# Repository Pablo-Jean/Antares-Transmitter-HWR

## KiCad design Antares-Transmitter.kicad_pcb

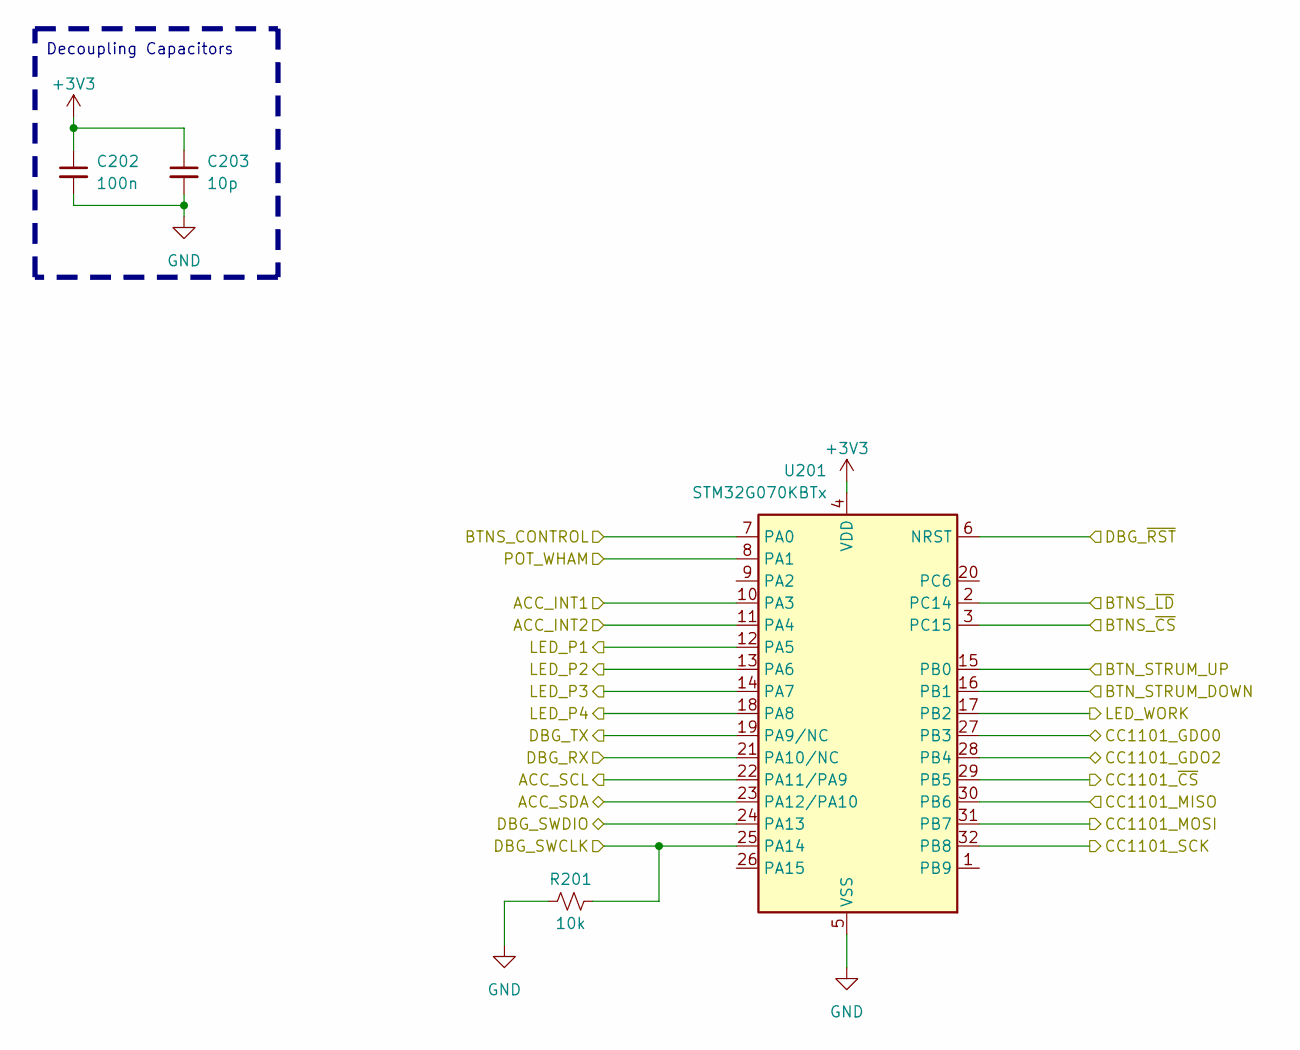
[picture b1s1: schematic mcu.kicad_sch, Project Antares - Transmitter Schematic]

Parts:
C202: 100n; C_0603_1608Metric; LCSC C14663
C203: 10p; C_0603_1608Metric; LCSC C1634
R201: 10k; R_0603_1608Metric; LCSC C25804
U201: STM32G070KBTx; LQFP-32_7x7mm_P0.8mm; LCSC C529339

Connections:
+3V3: C202.1, C203.1, U201.4 (VDD); also elsewhere on the board
/Accelerometer/ACC_INT1: U201.10 (PA3); also elsewhere on the board
/Accelerometer/ACC_INT2: U201.11 (PA4); also elsewhere on the board
/Accelerometer/ACC_SCL: U201.22 (PA11/PA9); also elsewhere on the board
/Accelerometer/ACC_SDA: U201.23 (PA12/PA10); also elsewhere on the board
/Control Buttons/BTNS_CONTROL: U201.7 (PA0); also elsewhere on the board
/Control Buttons/LED_WORK: U201.17 (PB2); also elsewhere on the board
/Debugging/DBG_RX: U201.21 (PA10/NC); also elsewhere on the board
/Debugging/DBG_SWCLK: R201.2, U201.25 (PA14); also elsewhere on the board
/Debugging/DBG_SWDIO: U201.24 (PA13); also elsewhere on the board
/Debugging/DBG_TX: U201.19 (PA9/NC); also elsewhere on the board
/Debugging/DBG_~RST: U201.6 (NRST); also elsewhere on the board
/LEDs/LED_P1: U201.12 (PA5); also elsewhere on the board
/LEDs/LED_P2: U201.13 (PA6); also elsewhere on the board
/LEDs/LED_P3: U201.14 (PA7); also elsewhere on the board
/LEDs/LED_P4: U201.18 (PA8); also elsewhere on the board
/MCU/BTN_STRUM_DOWN: U201.16 (PB1); also elsewhere on the board
/MCU/BTN_STRUM_UP: U201.15 (PB0); also elsewhere on the board
/MCU/CC1101_GDO0: U201.27 (PB3); also elsewhere on the board
/MCU/CC1101_GDO2: U201.28 (PB4); also elsewhere on the board
/MCU/CC1101_MOSI: U201.31 (PB7); also elsewhere on the board
/MCU/CC1101_~CS: U201.29 (PB5); also elsewhere on the board
/MCU/POT_WHAM: U201.8 (PA1); also elsewhere on the board
/Notes/HC165_DO: U201.30 (PB6); also elsewhere on the board
/Notes/HC165_LOAD: U201.2 (PC14); also elsewhere on the board
/Notes/HC165_SCK: U201.32 (PB8); also elsewhere on the board
/Notes/HC165_~CS: U201.3 (PC15); also elsewhere on the board
GND: C202.2, C203.2, R201.1, U201.5 (VSS); also elsewhere on the board

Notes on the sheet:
Decoupling Capacitors

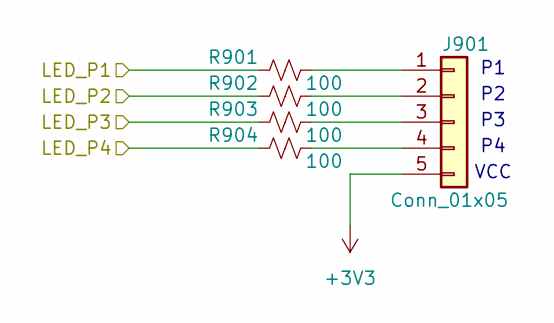
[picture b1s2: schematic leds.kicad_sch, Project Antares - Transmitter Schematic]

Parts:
J901: Conn_01x05; JST_XH_S5B-XH-A-1_1x05_P2.50mm_Horizontal; LCSC C2845508
R901, R902, R903, R904: 100; R_0603_1608Metric; LCSC C22775

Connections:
+3V3: J901.5; also elsewhere on the board
/LEDs/LED_P1: R901.1; also elsewhere on the board
/LEDs/LED_P2: R902.1; also elsewhere on the board
/LEDs/LED_P3: R903.1; also elsewhere on the board
/LEDs/LED_P4: R904.1; also elsewhere on the board
unnamed: J901.1, R901.2
unnamed: J901.2, R902.2
unnamed: J901.3, R903.2
unnamed: J901.4, R904.2

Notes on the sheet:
VCC

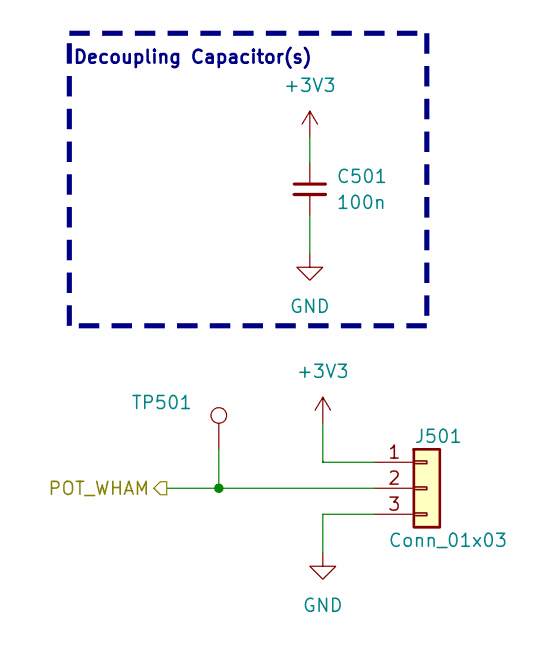
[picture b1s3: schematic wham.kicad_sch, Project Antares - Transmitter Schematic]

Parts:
C501: 100n; C_0603_1608Metric; LCSC C14663
J501: Conn_01x03; JST_XH_S3B-XH-A-1_1x03_P2.50mm_Horizontal; LCSC C2845506
TP501: TestPoint; TestPoint_Pad_D1.5mm

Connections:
+3V3: C501.1, J501.1; also elsewhere on the board
/MCU/POT_WHAM: J501.2, TP501.1; also elsewhere on the board
GND: C501.2, J501.3; also elsewhere on the board

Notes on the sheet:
Decoupling Capacitor(s)

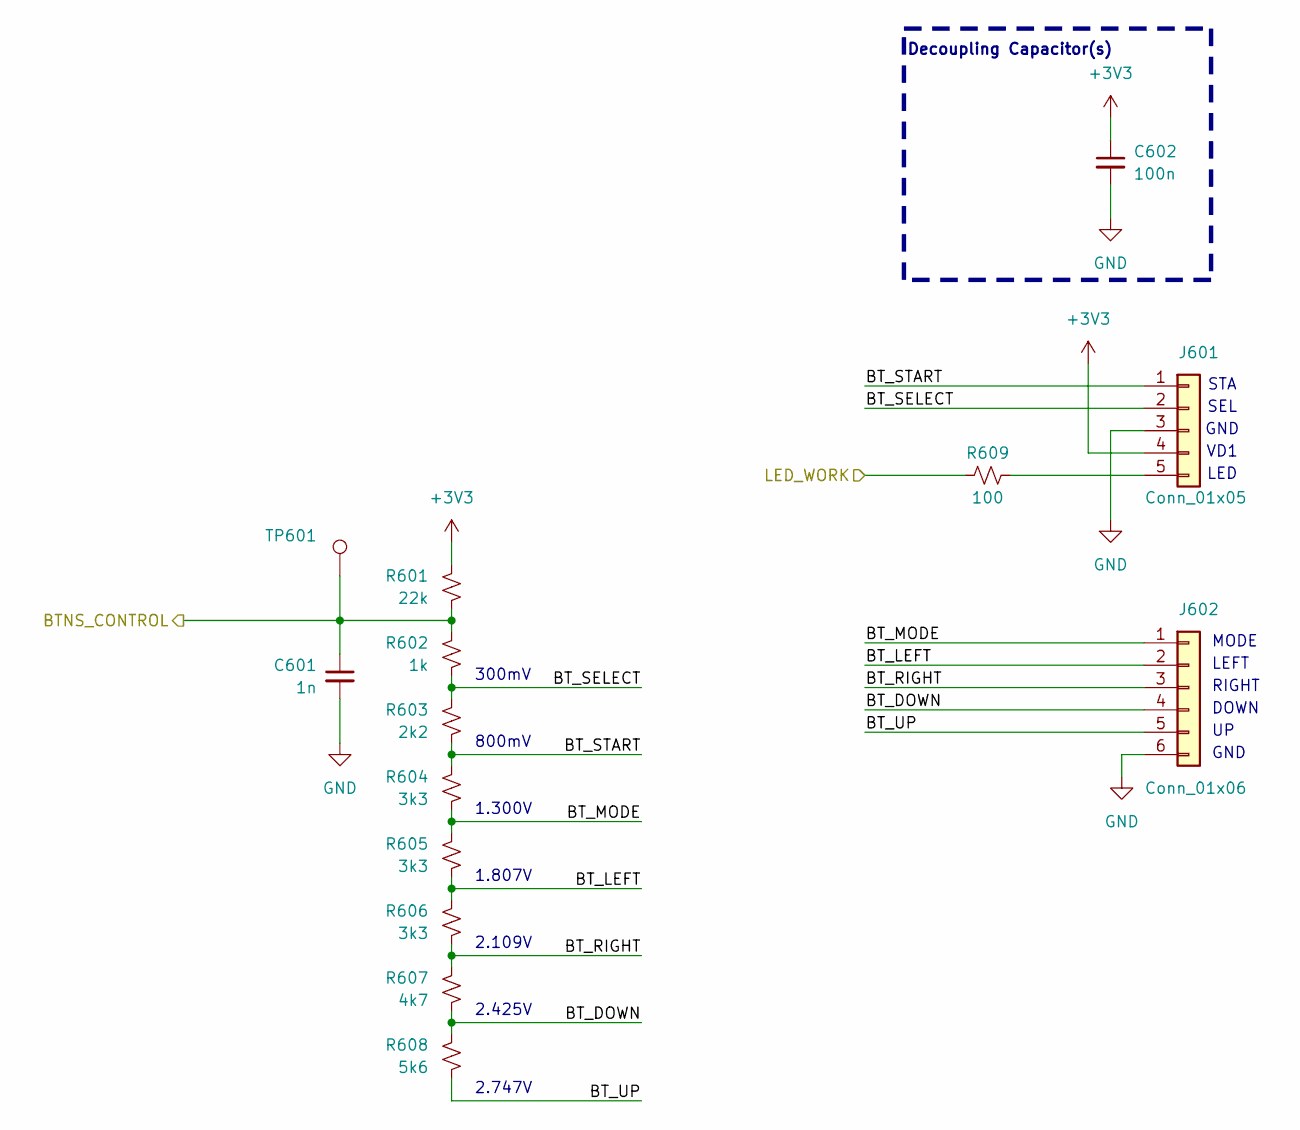
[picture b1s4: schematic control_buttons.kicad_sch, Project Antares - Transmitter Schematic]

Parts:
C601: 1n; C_0603_1608Metric; LCSC C1588
C602: 100n; C_0603_1608Metric; LCSC C14663
J601: Conn_01x05; JST_XH_S5B-XH-A-1_1x05_P2.50mm_Horizontal; LCSC C2845508
J602: Conn_01x06; JST_PH_S6B-PH-K_1x06_P2.00mm_Horizontal; LCSC C2908638
R601: 22k; R_0603_1608Metric; LCSC C31850
R602: 1k; R_0603_1608Metric; LCSC C21190
R603: 2k2; R_0603_1608Metric; LCSC C4190
R604, R605, R606: 3k3; R_0603_1608Metric; LCSC C22978
R607: 4k7; R_0603_1608Metric; LCSC C23162
R608: 5k6; R_0603_1608Metric; LCSC C23189
R609: 100; R_0603_1608Metric; LCSC C22775
TP601: TestPoint; TestPoint_Pad_D1.5mm

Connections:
+3V3: C602.1, J601.4, R601.1; also elsewhere on the board
/Control Buttons/BTNS_CONTROL: C601.1, R601.2, R602.1, TP601.1; also elsewhere on the board
/Control Buttons/BT_DOWN: J602.4, R607.2, R608.1
/Control Buttons/BT_LEFT: J602.2, R605.2, R606.1
/Control Buttons/BT_MODE: J602.1, R604.2, R605.1
/Control Buttons/BT_RIGHT: J602.3, R606.2, R607.1
/Control Buttons/BT_SELECT: J601.2, R602.2, R603.1
/Control Buttons/BT_START: J601.1, R603.2, R604.1
/Control Buttons/BT_UP: J602.5, R608.2
/Control Buttons/LED_WORK: R609.1; also elsewhere on the board
GND: C601.2, C602.2, J601.3, J602.6; also elsewhere on the board
unnamed: J601.5, R609.2

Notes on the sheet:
SEL
1.807V
VD1
RIGHT
MODE
800mV
Decoupling Capacitor(s)
1.300V
GND
LEFT
2.425V
STA
DOWN
300mV
LED
2.109V
2.747V

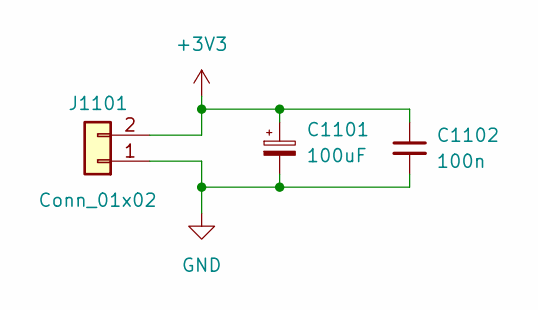
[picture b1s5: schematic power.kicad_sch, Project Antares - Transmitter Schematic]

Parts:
C1101: 100uF; CP_Elec_6.3x4.5; LCSC C5374787
C1102: 100n; C_0603_1608Metric; LCSC C14663
J1101: Conn_01x02; JST_XH_S2B-XH-A-1_1x02_P2.50mm_Horizontal; LCSC C33132

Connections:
+3V3: C1101.1, C1102.1, J1101.2; also elsewhere on the board
GND: C1101.2, C1102.2, J1101.1; also elsewhere on the board

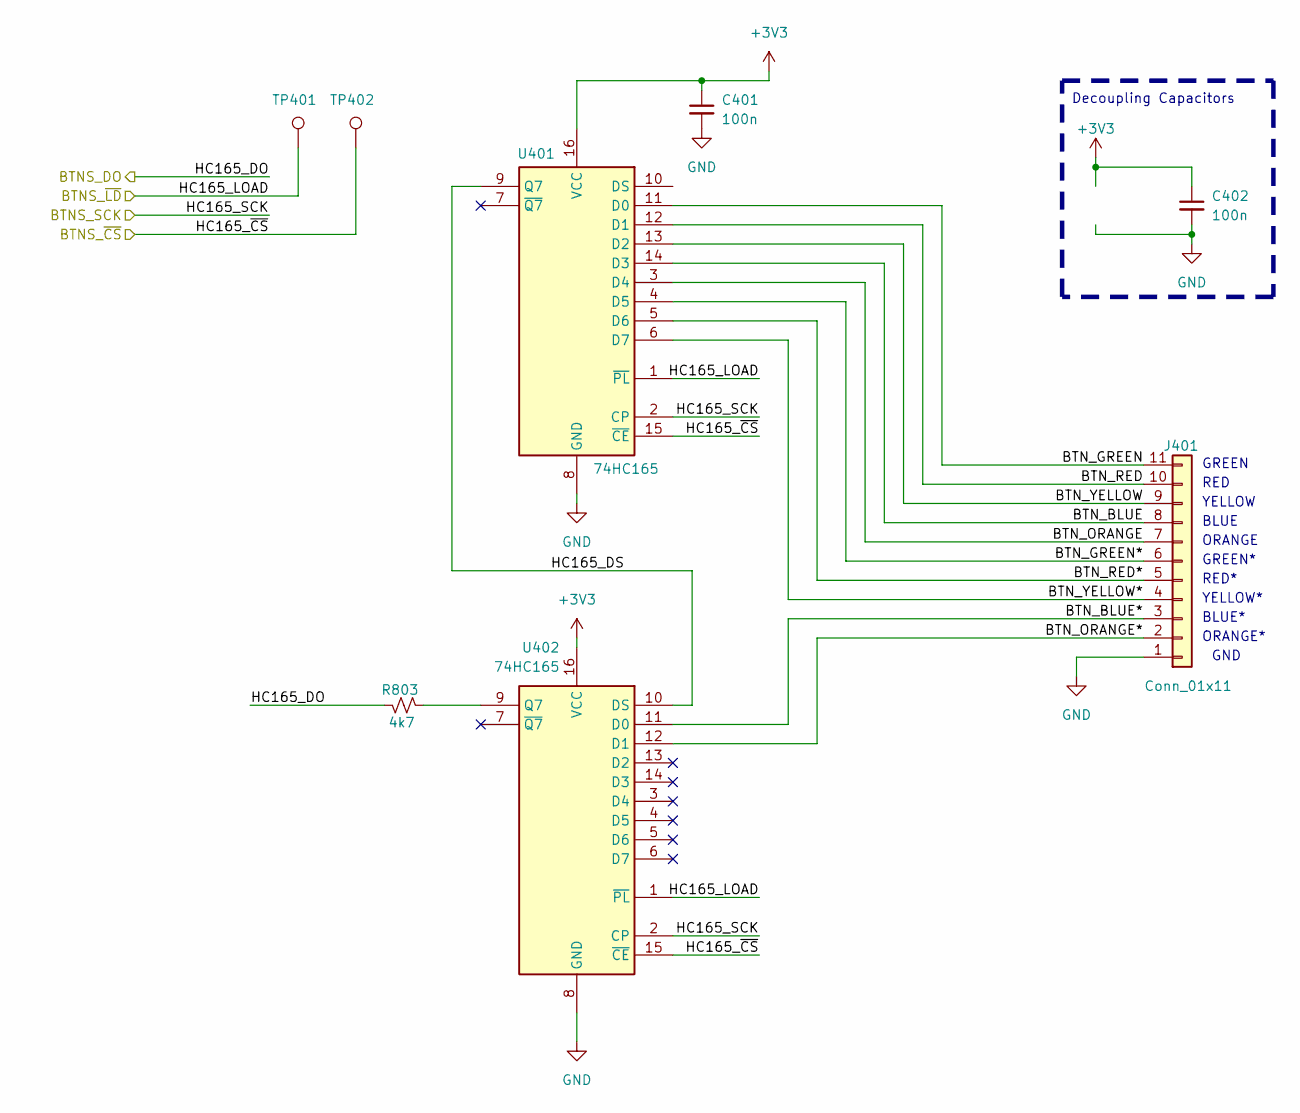
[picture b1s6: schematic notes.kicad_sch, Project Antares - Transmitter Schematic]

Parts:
C401, C402: 100n; C_0603_1608Metric; LCSC C14663
J401: Conn_01x11; JST_XH_S11B-XH-A-1_1x11_P2.50mm_Horizontal; LCSC C2845514
R803: 4k7; R_0603_1608Metric; LCSC C23162
TP401, TP402: TestPoint; TestPoint_Pad_D1.5mm
U401, U402: 74HC165; TSSOP-16_4.4x5mm_P0.65mm; LCSC C80696

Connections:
+3V3: C401.1, C402.1, U401.16 (VCC), U402.16 (VCC); also elsewhere on the board
/Notes/BTN_BLUE: J401.8, U401.14 (D3)
/Notes/BTN_BLUE*: J401.3, U402.11 (D0)
/Notes/BTN_GREEN: J401.11, U401.11 (D0)
/Notes/BTN_GREEN*: J401.6, U401.4 (D5)
/Notes/BTN_ORANGE: J401.7, U401.3 (D4)
/Notes/BTN_ORANGE*: J401.2, U402.12 (D1)
/Notes/BTN_RED: J401.10, U401.12 (D1)
/Notes/BTN_RED*: J401.5, U401.5 (D6)
/Notes/BTN_YELLOW: J401.9, U401.13 (D2)
/Notes/BTN_YELLOW*: J401.4, U401.6 (D7)
/Notes/HC165_DS: U401.9 (Q7), U402.10 (DS)
/Notes/HC165_LOAD: TP401.1, U401.1 (~PL), U402.1 (~PL); also elsewhere on the board
/Notes/HC165_SCK: U401.2 (CP), U402.2 (CP); also elsewhere on the board
/Notes/HC165_~CS: TP402.1, U401.15 (~CE), U402.15 (~CE); also elsewhere on the board
GND: C401.2, C402.2, J401.1, U401.8 (GND), U401.10 (DS), U402.8 (GND); also elsewhere on the board
unnamed: R803.2, U402.9 (Q7)

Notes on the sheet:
ORANGE*
GREEN
YELLOW
ORANGE
YELLOW*
GREEN*
BLUE
GND
Decoupling Capacitors
RED
RED*
BLUE*

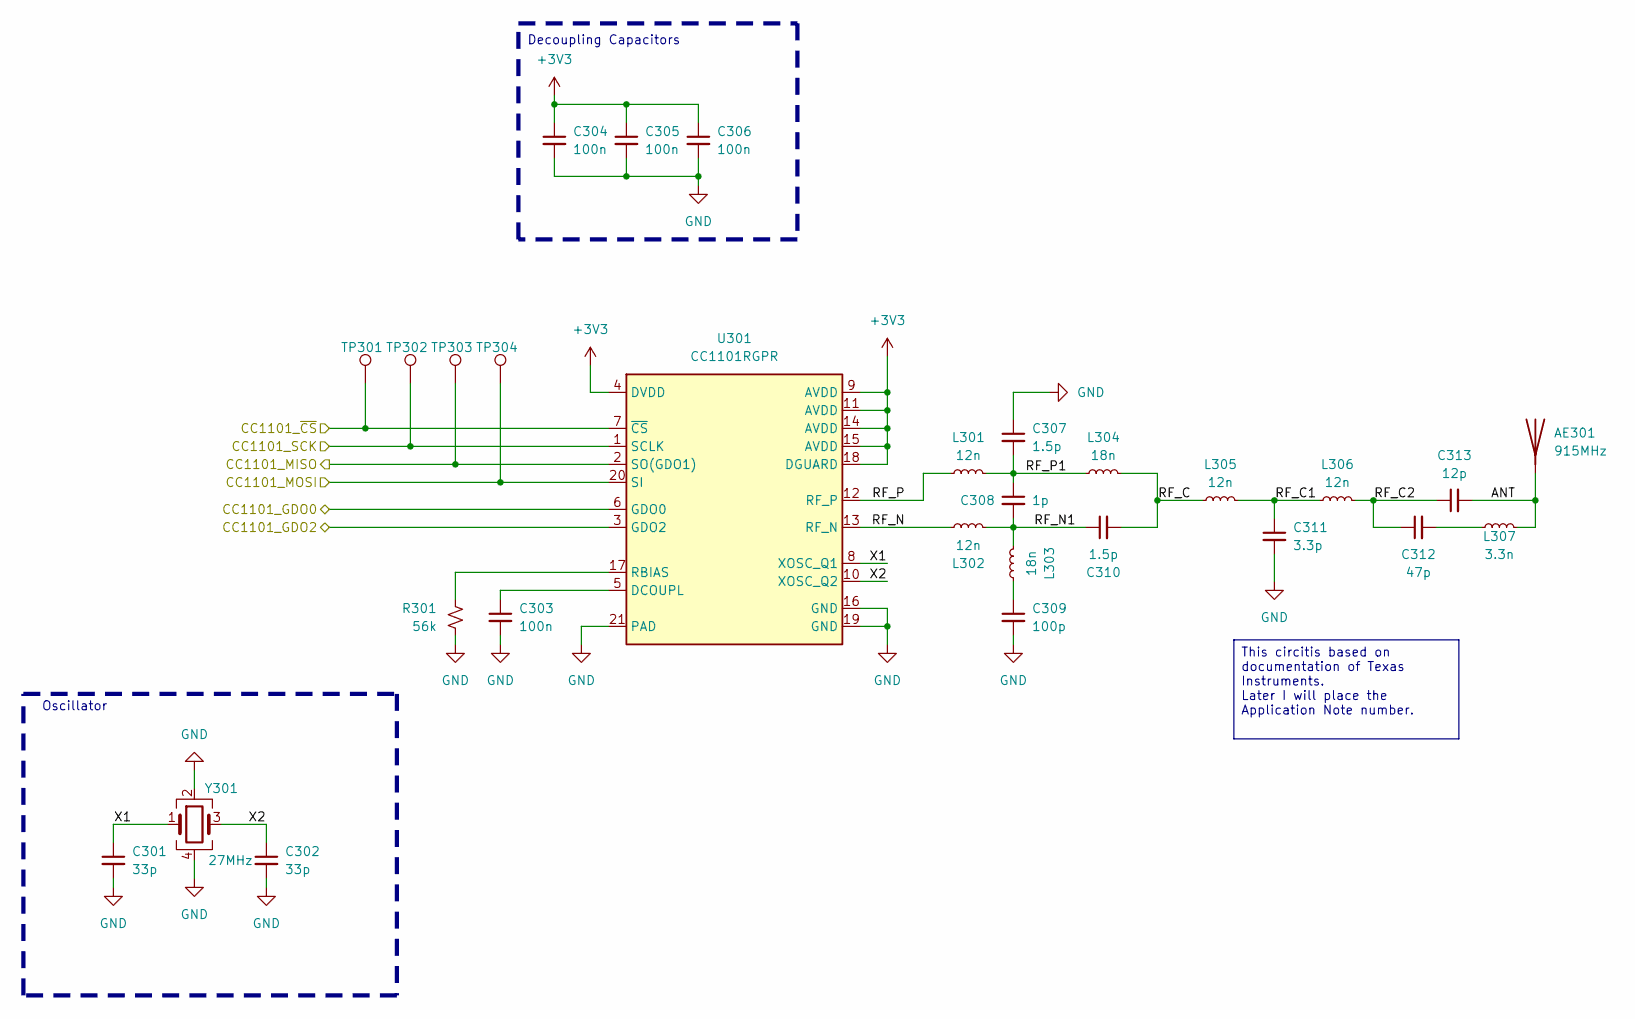
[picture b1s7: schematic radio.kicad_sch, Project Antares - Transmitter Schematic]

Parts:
AE301: 915MHz; Texas_SWRA416_868MHz_915MHz
C301, C302: 33p; C_0603_1608Metric; LCSC C1663
C303, C304, C305, C306: 100n; C_0603_1608Metric; LCSC C14663
C307, C310: 1.5p; C_0603_1608Metric; LCSC C519100
C308: 1p; C_0603_1608Metric; LCSC C115062
C309: 100p; C_0603_1608Metric; LCSC C14858
C311: 3.3p; C_0603_1608Metric; LCSC C282249
C312: 47p; C_0603_1608Metric; LCSC C1671
C313: 12p; C_0603_1608Metric; LCSC C38523
L301, L302, L305, L306: 12n; L_0603_1608Metric; LCSC C75656
L303, L304: 18n; L_0603_1608Metric; LCSC C90206
L307: 3.3n; L_0603_1608Metric; LCSC C1029
R301: 56k; R_0603_1608Metric; LCSC C23206
TP301, TP302, TP303, TP304: TestPoint; TestPoint_Pad_D1.5mm
U301: CC1101RGPR; QFN-20-1EP_4x4mm_P0.5mm_EP2.5x2.5mm_ThermalVias; LCSC C29953
Y301: 27MHz; Crystal_SMD_3225-4Pin_3.2x2.5mm; LCSC C9008

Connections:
+3V3: C304.1, C305.1, C306.1, U301.4 (DVDD), U301.9 (AVDD), U301.11 (AVDD), U301.14 (AVDD), U301.15 (AVDD), U301.18 (DGUARD); also elsewhere on the board
/MCU/CC1101_GDO0: U301.6 (GDO0); also elsewhere on the board
/MCU/CC1101_GDO2: U301.3 (GDO2); also elsewhere on the board
/MCU/CC1101_MOSI: TP304.1, U301.20 (SI); also elsewhere on the board
/MCU/CC1101_~CS: TP301.1, U301.7 (~CS); also elsewhere on the board
/Notes/HC165_DO: TP303.1, U301.2 (SO(GDO1)); also elsewhere on the board
/Notes/HC165_SCK: TP302.1, U301.1 (SCLK); also elsewhere on the board
/Radio 915MHz/ANT: AE301.1 (A), C313.2, L307.2
/Radio 915MHz/RF_C: C310.2, L304.2, L305.1
/Radio 915MHz/RF_C1: C311.1, L305.2, L306.1
/Radio 915MHz/RF_C2: C312.1, C313.1, L306.2
/Radio 915MHz/RF_N: L302.1, U301.13 (RF_N)
/Radio 915MHz/RF_N1: C308.2, C310.1, L302.2, L303.2
/Radio 915MHz/RF_P: L301.1, U301.12 (RF_P)
/Radio 915MHz/RF_P1: C307.2, C308.1, L301.2, L304.1
/Radio 915MHz/X1: C301.1, U301.8 (XOSC_Q1), Y301.1
/Radio 915MHz/X2: C302.1, U301.10 (XOSC_Q2), Y301.3
GND: C301.2, C302.2, C303.2, C304.2, C305.2, C306.2, C307.1, C309.2, C311.2, R301.2, U301.16 (GND), U301.19 (GND), U301.21 (PAD), Y301.2, Y301.4; also elsewhere on the board
unnamed: C309.1, L303.1
unnamed: C312.2, L307.1
unnamed: C303.1, U301.5 (DCOUPL)
unnamed: R301.1, U301.17 (RBIAS)

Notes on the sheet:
Decoupling Capacitors
Oscillator
This circitis based on documentation of Texas Instruments. Later I will place the Application Note number.

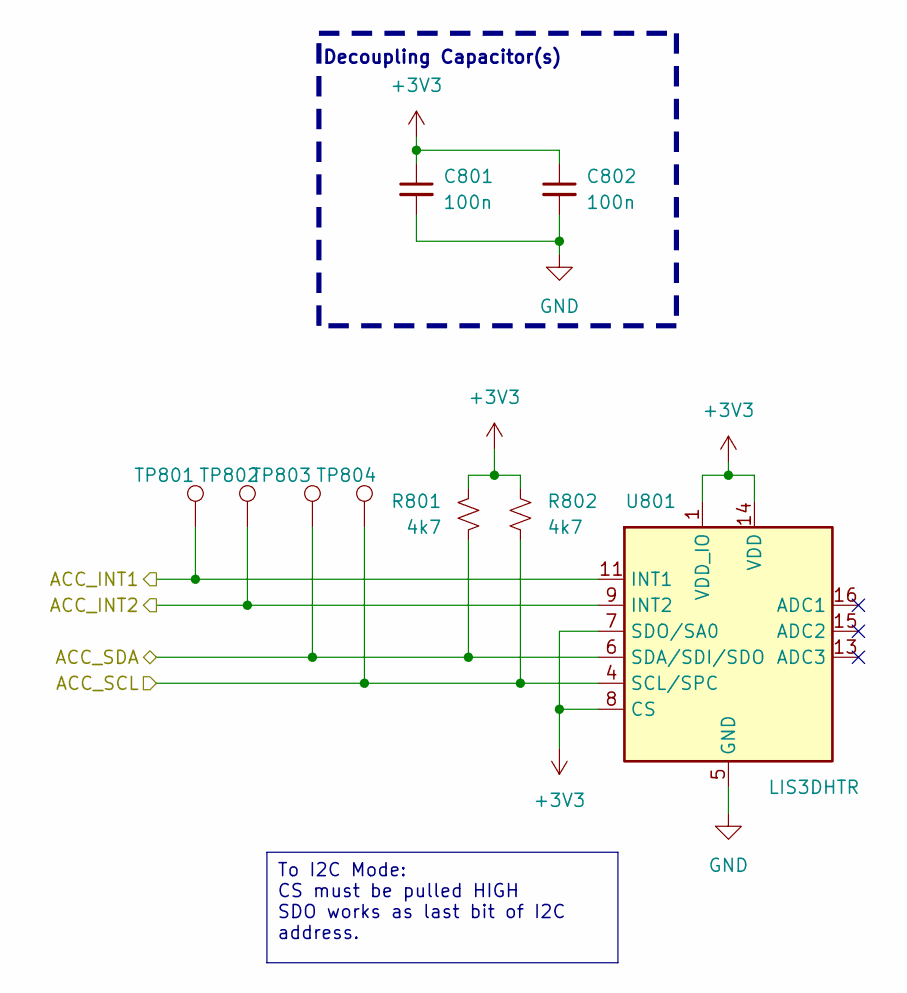
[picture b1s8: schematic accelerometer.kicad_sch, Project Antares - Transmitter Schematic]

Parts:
C801, C802: 100n; C_0603_1608Metric; LCSC C14663
R801, R802: 4k7; R_0603_1608Metric; LCSC C23162
TP801, TP802, TP803, TP804: TestPoint; TestPoint_Pad_D1.5mm
U801: LIS3DHTR; LGA-16_3x3mm_P0.5mm_LayoutBorder3x5y; LCSC C15134

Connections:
+3V3: C801.1, C802.1, R801.1, R802.1, U801.1 (VDD_IO), U801.7 (SDO/SA0), U801.8 (CS), U801.14 (VDD); also elsewhere on the board
/Accelerometer/ACC_INT1: TP801.1, U801.11 (INT1); also elsewhere on the board
/Accelerometer/ACC_INT2: TP802.1, U801.9 (INT2); also elsewhere on the board
/Accelerometer/ACC_SCL: R802.2, TP804.1, U801.4 (SCL/SPC); also elsewhere on the board
/Accelerometer/ACC_SDA: R801.2, TP803.1, U801.6 (SDA/SDI/SDO); also elsewhere on the board
GND: C801.2, C802.2, U801.5 (GND), U801.10 (GND), U801.12 (GND); also elsewhere on the board

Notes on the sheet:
Decoupling Capacitor(s)
To I2C Mode: CS must be pulled HIGH SDO works as last bit of I2C address.

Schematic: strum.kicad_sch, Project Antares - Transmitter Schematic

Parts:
C701, C702: 100n; C_0603_1608Metric; LCSC C14663
R701, R702: 100; R_0603_1608Metric; LCSC C22775
R703, R704: 10k; R_0603_1608Metric; LCSC C25804
SW701: DOWN; SW_Cherry_MX_1.00u_PCB; LCSC C404351
SW702: UP; SW_Cherry_MX_1.00u_PCB; LCSC C404351
TP701, TP702: TestPoint; TestPoint_Pad_D1.5mm

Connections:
+3V3: R703.1, R704.1; also elsewhere on the board
/MCU/BTN_STRUM_DOWN: C701.1, R701.1, TP701.1; also elsewhere on the board
/MCU/BTN_STRUM_UP: C702.1, R702.1, TP702.1; also elsewhere on the board
/Strum bar/SW_DN: R701.2, R703.2, SW701.1 (A)
/Strum bar/SW_UP: R702.2, R704.2, SW702.1 (A)
GND: C701.2, C702.2, SW701.2 (B), SW702.2 (B); also elsewhere on the board

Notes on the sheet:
tFULL = 5*R*C tFULL = 5*100*100n tFULL = 50us Maybe is good to have filtering and response.

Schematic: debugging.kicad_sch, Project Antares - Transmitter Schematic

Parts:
J1001: Debugger Pin; PinHeader_1x07_P2.54mm_Vertical
R1001, R1002, R1003, R1004, R1005: 10; R_0603_1608Metric; LCSC C22859

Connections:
+3V3: J1001.1; also elsewhere on the board
/Debugging/DBG_RX: R1002.1; also elsewhere on the board
/Debugging/DBG_SWCLK: R1005.1; also elsewhere on the board
/Debugging/DBG_SWDIO: R1004.1; also elsewhere on the board
/Debugging/DBG_TX: R1001.1; also elsewhere on the board
/Debugging/DBG_~RST: R1003.1; also elsewhere on the board
/Debugging/RX: J1001.3, R1002.2
/Debugging/SWCLK: J1001.6, R1005.2
/Debugging/SWDIO: J1001.5, R1004.2
/Debugging/TX: J1001.2, R1001.2
/Debugging/~RST: J1001.4, R1003.2
GND: J1001.7; also elsewhere on the board

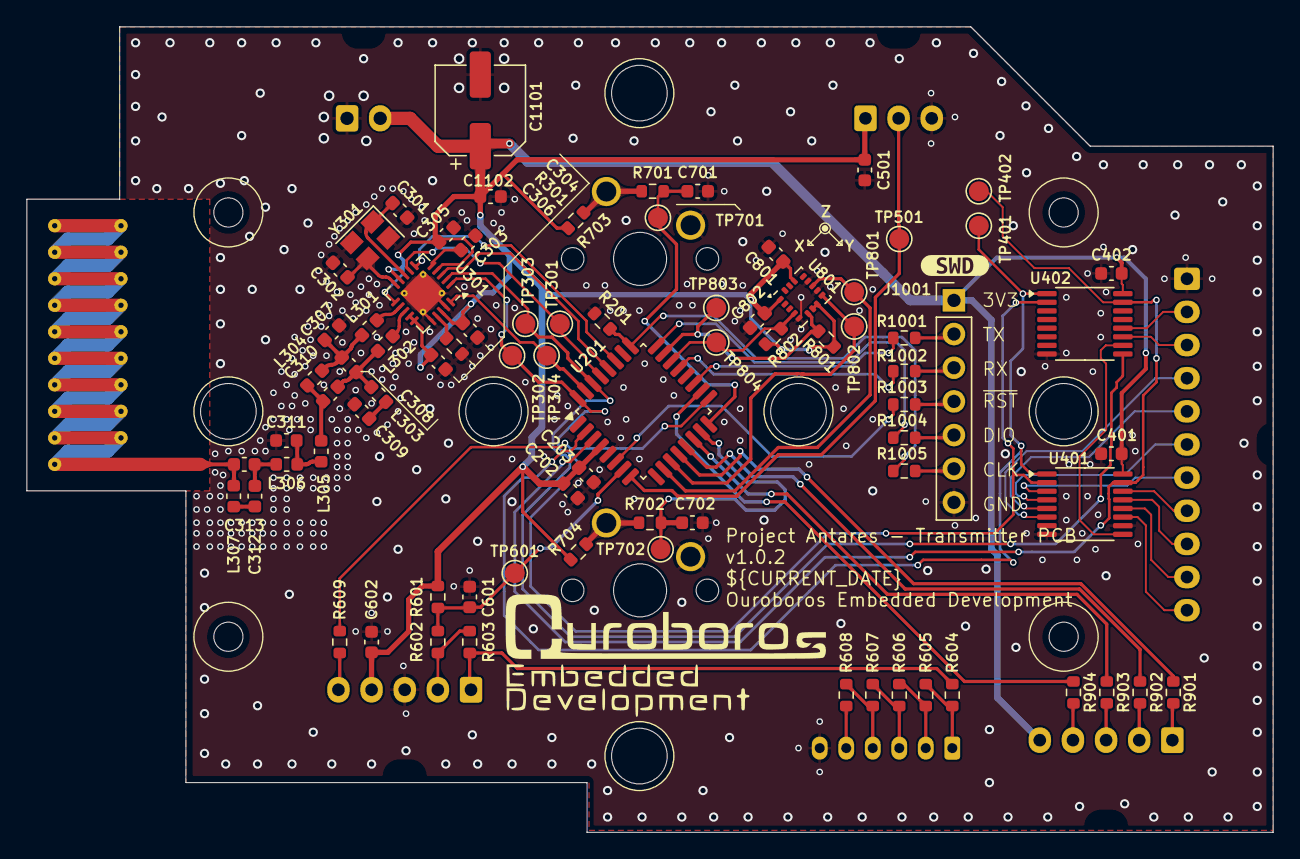
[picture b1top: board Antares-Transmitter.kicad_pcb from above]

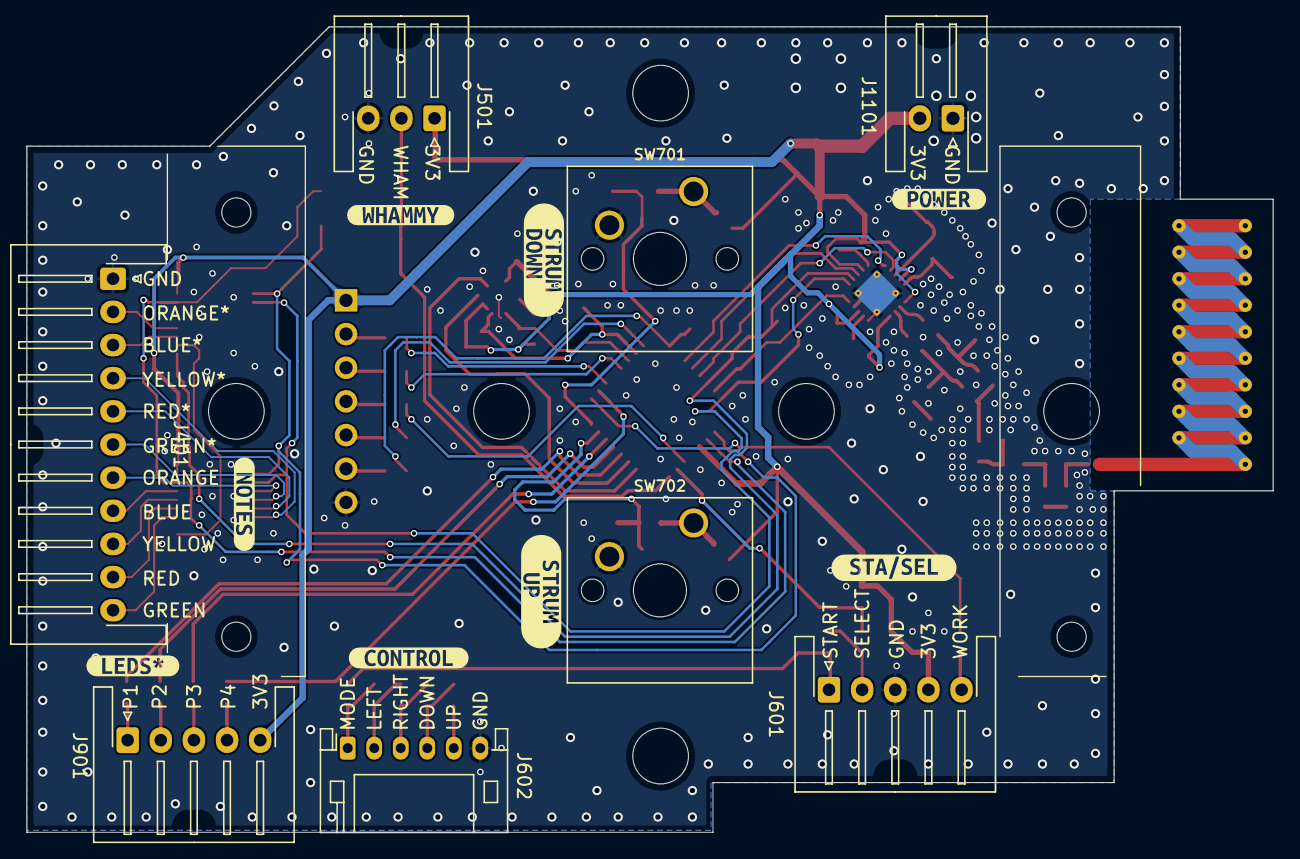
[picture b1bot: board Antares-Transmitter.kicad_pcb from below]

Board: 2 copper layers, 94.0 x 60.8 mm, 98 parts (16 on the bottom side), 72 nets.

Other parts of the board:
kibuzzard-66C9DF62: G***; kibuzzard-66C9DF62
kibuzzard-66C9DFEC: G***; kibuzzard-66C9DFEC
kibuzzard-66C9E0B9: G***; kibuzzard-66C9E0B9
kibuzzard-66C9E0F4: G***; kibuzzard-66C9E0F4
kibuzzard-66C9E01B: G***; kibuzzard-66C9E01B
kibuzzard-66C9E05B: G***; kibuzzard-66C9E05B
kibuzzard-66C9E07F: G***; kibuzzard-66C9E07F
kibuzzard-66C9E09D: G***; kibuzzard-66C9E09D
kibuzzard-66C9E100: G***; kibuzzard-66C9E100

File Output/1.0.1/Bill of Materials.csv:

"Designator","Value","Footprint","Qty","DNP","LCSC","PN"
"AE301","915MHz","RF_Antenna:Texas_SWRA416_868MHz_915MHz","1","","",""
"C202,C303,C304,C305,C306,C401,C402,C501,C602,C701,C702,C801,C802,C1102","100n","Capacitor_SMD:C_0603_1608Metric","14","","C14663","CC0603KRX7R9BB104"
"C203","10p","Capacitor_SMD:C_0603_1608Metric","1","","C106245","CC0603JRNPO9BN100"
"C301,C302","33p","Capacitor_SMD:C_0603_1608Metric","2","","C107047","CC0603JRNPO9BN330"
"C307,C310","1.5p","Capacitor_SMD:C_0603_1608Metric","2","","C519100","CC0603BRNPO9BN1R5"
"C308","1p","Capacitor_SMD:C_0603_1608Metric","1","","C115062","CC0603BRNPO9BN1R0"
"C309","100p","Capacitor_SMD:C_0603_1608Metric","1","","C14665","CC0603JRNPO9BN101"
"C311","3.3p","Capacitor_SMD:C_0603_1608Metric","1","","C282249","CC0603CRNPO9BN3R3"
"C312","47p","Capacitor_SMD:C_0603_1608Metric","1","","C105622","CC0603JRNPO9BN470"
"C313","12p","Capacitor_SMD:C_0603_1608Metric","1","","C107034","CC0603JRNPO9BN120"
"C601","1n","Capacitor_SMD:C_0603_1608Metric","1","","C100040","CC0603KRX7R9BB102"
"C1101","100uF","Capacitor_SMD:CP_Elec_6.3x4.5","1","","C5374787","126RV0054"
"J401","Conn_01x11","Connector_JST:JST_XA_S11B-XASK-1_1x11_P2.50mm_Horizontal","1","","C2845514","HC-XHB-11AW"
"J501","Conn_01x03","Connector_JST:JST_XA_S03B-XASK-1_1x03_P2.50mm_Horizontal","1","","C2845506","HC-XHB-3AW"
"J601,J901","Conn_01x05","Connector_JST:JST_XA_S05B-XASK-1_1x05_P2.50mm_Horizontal","2","","C2845508","HC-XHB-5AW"
"J602","Conn_01x06","JST_PH_S6B-PH-K_1x06_P2.00mm_Horizontal","1","","C2908638","PH-6AW"
"J1001","Debugger Pin","Connector_PinHeader_2.54mm:PinHeader_1x07_P2.54mm_Vertical","1","","",""
"J1101","Conn_01x02","Connector_JST:JST_XA_S02B-XASK-1_1x02_P2.50mm_Horizontal","1","","C33132","XH-2AW"
"L301,L302,L305,L306","12n","Inductor_SMD:L_0603_1608Metric","4","","C75656","VHF160808H12NJT"
"L303,L304","18n","Inductor_SMD:L_0603_1608Metric","2","","C90206","VHF160808H18NJT"
"L307","3.3n","Inductor_SMD:L_0603_1608Metric","1","","C1029","VHF160808H3N3ST"
"R201,R703,R704","10k","Resistor_SMD:R_0603_1608Metric","3","","C25804","0603WAF1002T5E"
"R301","56k","Resistor_SMD:R_0603_1608Metric","1","","C23206","0603WAF5602T5E"
"R601","22k","Resistor_SMD:R_0603_1608Metric","1","","C31850","0603WAF2202T5E"
"R602","1k","Resistor_SMD:R_0603_1608Metric","1","","C21190","0603WAF1001T5E"
"R603","2k2","Resistor_SMD:R_0603_1608Metric","1","","C4190","0603WAF2201T5E"
"R604,R605,R606","3k3","Resistor_SMD:R_0603_1608Metric","3","","C22978","0603WAF3301T5E"
"R607,R801,R802","4k7","Resistor_SMD:R_0603_1608Metric","3","","C99782","RC0603FR-074K7L"
"R608","5k6","Resistor_SMD:R_0603_1608Metric","1","","C23189","0603WAF5601T5E"
"R609,R701,R702,R901,R902,R903,R904","100","Resistor_SMD:R_0603_1608Metric","7","","C22775","0603WAF1000T5E"
"R1001,R1002,R1003,R1004,R1005","10","Resistor_SMD:R_0603_1608Metric","5","","C22859","0603WAF100JT5E"
"SW701","DOWN","Button_Switch_Keyboard:SW_Cherry_MX_1.00u_PCB","1","","C404351","CPG151101S21"
"SW702","UP","Button_Switch_Keyboard:SW_Cherry_MX_1.00u_PCB","1","","C404351","CPG151101S21"
"TP301,TP302,TP303,TP304,TP401,TP402,TP501,TP601,TP701,TP702,TP801,TP802,TP803,TP804","TestPoint","TestPoint:TestPoint_Pad_D1.5mm","14","","",""
"U201","STM32G070KBTx","Package_QFP:LQFP-32_7x7mm_P0.8mm","1","","C529339","STM32G070KBT6"
"U301","CC1101RGPR","Package_DFN_QFN:QFN-20-1EP_4x4mm_P0.5mm_EP2.5x2.5mm_ThermalVias","1","","C29953","CC1101RGPR"
"U401,U402","74HC165","Package_SO:TSSOP-16_4.4x5mm_P0.65mm","2","","C80696","74HC165PW,118"
"U801","LIS3DHTR","Package_LGA:LGA-16_3x3mm_P0.5mm_LayoutBorder3x5y","1","","C15134","LIS3DHTR"
"Y301","27MHz","Crystal:Crystal_SMD_3225-4Pin_3.2x2.5mm","1","","C9008","X322527MSB4SI"

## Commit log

2024-08-24 :tada: first commit
2024-08-24 :package: finished version 1.0.0, generated production files
2024-08-24 t:art: fixed noted reading, using 75hc165 for Input expander
2024-08-24 :package: generated v1.0.1 production files
2024-08-24 fixed reference designator BOM export
2024-08-25 :minidisc: fixed some silkscreen, added vias and updated LCSC PNs with Basic components
2024-08-26 fixed v1.0.2 pcb and files
2024-09-04 :memo: added schematic model
2025-12-22 small fixes
